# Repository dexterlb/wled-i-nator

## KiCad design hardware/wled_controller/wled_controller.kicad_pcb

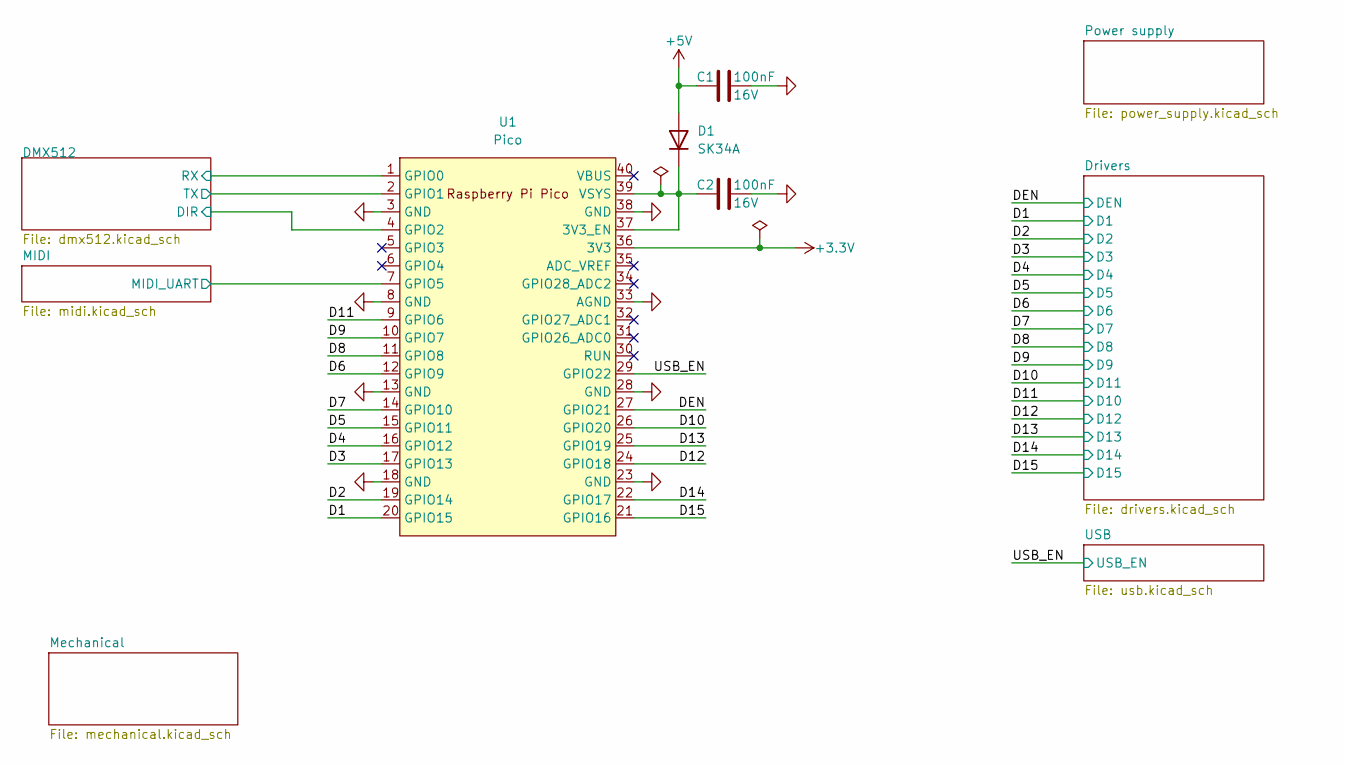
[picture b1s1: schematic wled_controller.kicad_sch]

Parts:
C1, C2: 100nF; C_0805_2012Metric; Part C 100nF 16V 0805
D1: SK34A; D_SMA; Part SK34A
U1: Pico; RPi_Pico_TH; Part 2x Header_01x20

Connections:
+3.3V: U1.36 (3V3); also elsewhere on the board
+5V: C1.1, D1.2 (A); also elsewhere on the board
/D1: U1.20 (GPIO15); also elsewhere on the board
/D2: U1.19 (GPIO14); also elsewhere on the board
/D3: U1.17 (GPIO13); also elsewhere on the board
/D4: U1.16 (GPIO12); also elsewhere on the board
/D5: U1.15 (GPIO11); also elsewhere on the board
/D6: U1.12 (GPIO9); also elsewhere on the board
/D7: U1.14 (GPIO10); also elsewhere on the board
/D8: U1.11 (GPIO8); also elsewhere on the board
/D9: U1.10 (GPIO7); also elsewhere on the board
/D10: U1.26 (GPIO20); also elsewhere on the board
/D11: U1.9 (GPIO6); also elsewhere on the board
/D12: U1.24 (GPIO18); also elsewhere on the board
/D13: U1.25 (GPIO19); also elsewhere on the board
/D14: U1.22 (GPIO17); also elsewhere on the board
/D15: U1.21 (GPIO16); also elsewhere on the board
/DEN: U1.27 (GPIO21); also elsewhere on the board
/DMX512/DIR: U1.4 (GPIO2); also elsewhere on the board
/DMX512/RX: U1.1 (GPIO0); also elsewhere on the board
/DMX512/TX: U1.2 (GPIO1); also elsewhere on the board
/MIDI/MIDI_UART: U1.7 (GPIO5); also elsewhere on the board
/USB_EN: U1.29 (GPIO22); also elsewhere on the board
GND: C1.2, C2.2, U1.3 (GND), U1.8 (GND), U1.13 (GND), U1.18 (GND), U1.23 (GND), U1.28 (GND), U1.33 (AGND), U1.38 (GND); also elsewhere on the board
unnamed: C2.1, D1.1 (K), U1.37 (3V3_EN), U1.39 (VSYS)

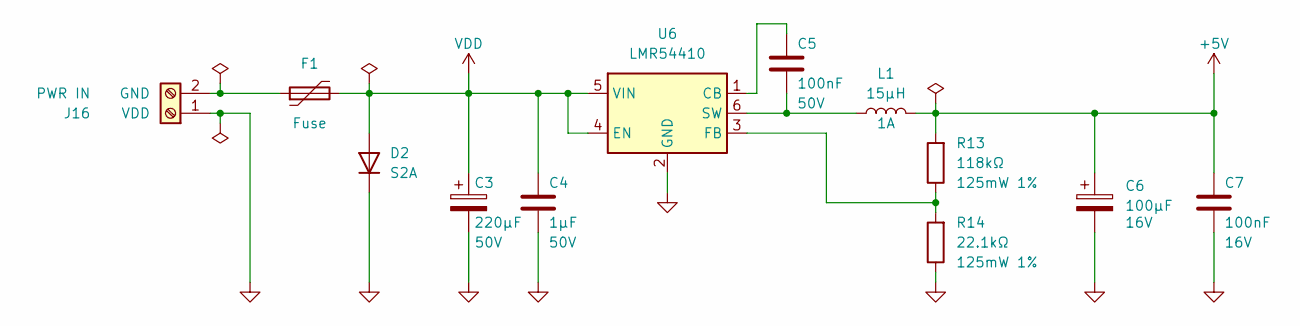
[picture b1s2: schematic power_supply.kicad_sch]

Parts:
C3: 220μF; CP_Radial_D10.0mm_P5.00mm; Part C 220μF 50V P5
C4: 1μF; C_0805_2012Metric; Part C 1μF 50V 0805
C5: 100nF; C_0805_2012Metric; Part C 100nF 50V 0805
C6: 100μF; CP_Radial_D5.0mm_P2.00mm; Part C 100μF 16V P2
C7: 100nF; C_0805_2012Metric; Part C 100nF 16V 0805
D2: S2A; D_SMB; Part S2A; LCSC C7420368
F1: Fuse; Fuseholder_FS002; Part 2x FS-002
J16: Screw_Terminal_01x02; TerminalBlock_1x02_P5.00mm_Horizontal; Part DG127-5.0-02P-14-00AH
L1: 15μH; L_Changjiang_FNR6045S; Part NRS6045T150MMGK
R13: 118kΩ; R_0805_2012Metric; Part R 118kΩ 125mW 1% 0805
R14: 22.1kΩ; R_0805_2012Metric; Part R 22.1kΩ 125mW 1% 0805
U6: LMR54410; SOT-23-6; Part LMR54410FDBVR

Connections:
+5V: C6.1, C7.1, L1.2, R13.2; also elsewhere on the board
GND: C3.2, C4.2, C6.2, C7.2, D2.1 (K), J16.1, R14.1, U6.2 (GND); also elsewhere on the board
unnamed: F1.1, J16.2
unnamed: C5.1, U6.1 (CB)
unnamed: R13.1, R14.2, U6.3 (FB)
unnamed: C5.2, L1.1, U6.6 (SW)
VDD: C3.1, C4.1, D2.2 (A), F1.2, U6.4 (EN), U6.5 (VIN); also elsewhere on the board

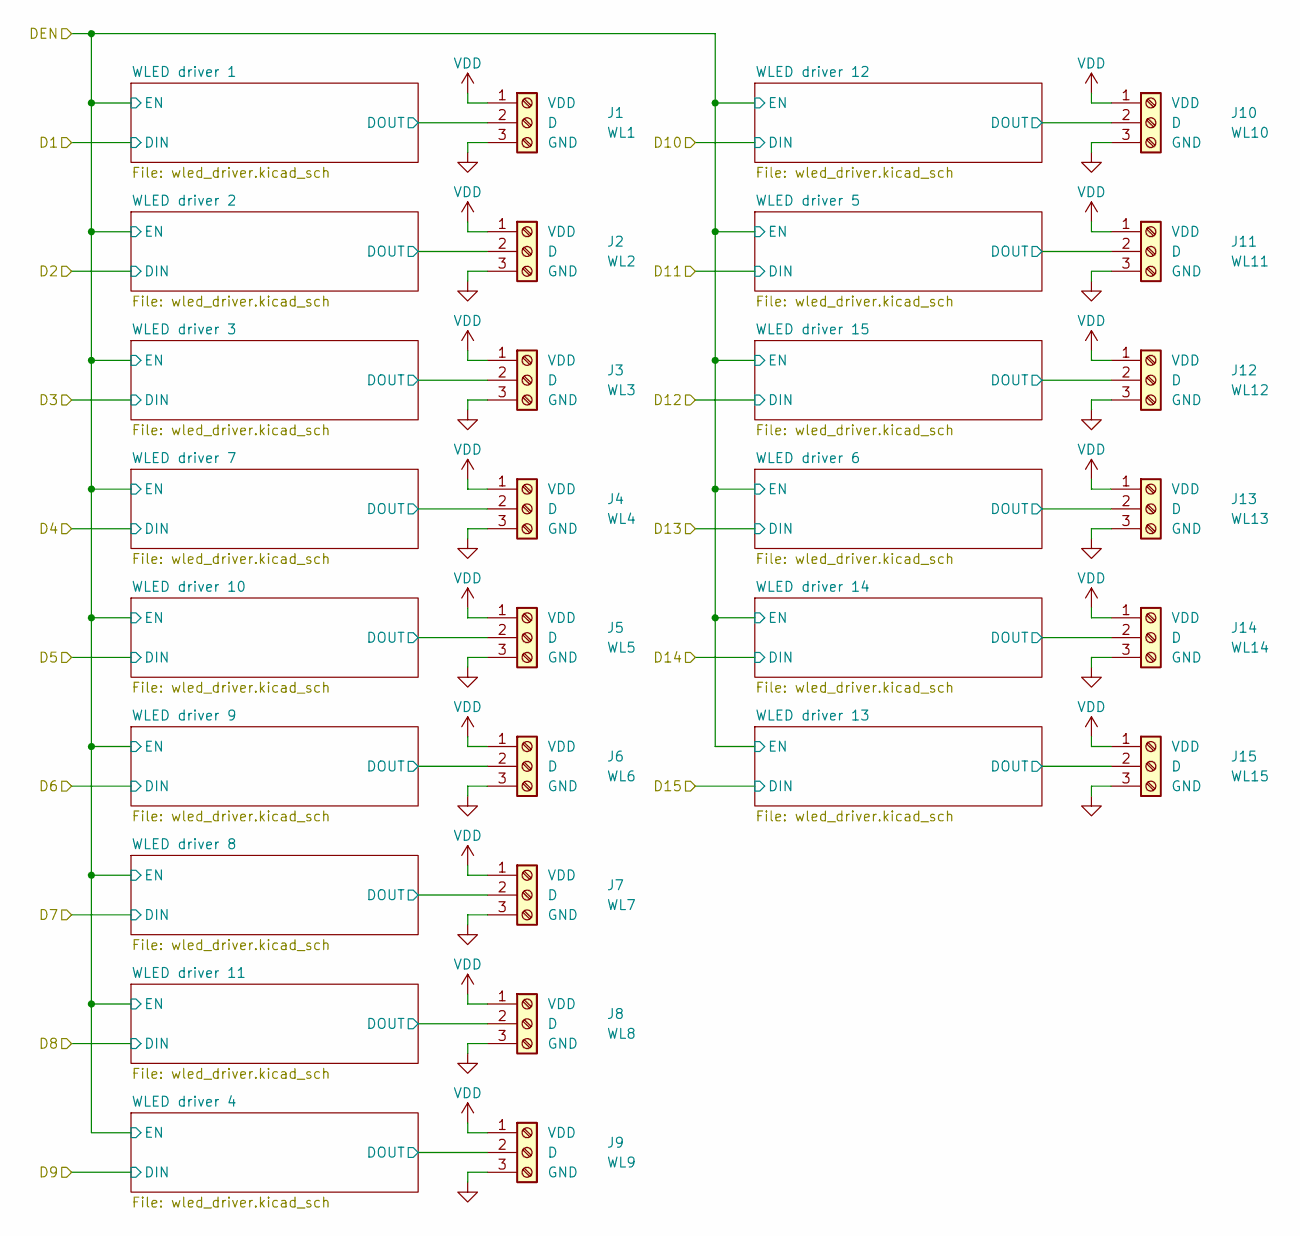
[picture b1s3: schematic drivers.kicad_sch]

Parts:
J1, J2, J3, J4, J5, J6, J7, J8, J9, J10, J11, J12, J13, J14, J15: Screw_Terminal_01x03; TerminalBlock_Degson_1x03_P3.50mm_Horizontal; Part 15EDGRC-3.5-03P-14-00AH, 15EDGK-3.5-03P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

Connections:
/Drivers/WLED driver 1/DOUT: J1.2; also elsewhere on the board
/Drivers/WLED driver 2/DOUT: J2.2; also elsewhere on the board
/Drivers/WLED driver 3/DOUT: J3.2; also elsewhere on the board
/Drivers/WLED driver 4/DOUT: J9.2; also elsewhere on the board
/Drivers/WLED driver 5/DOUT: J11.2; also elsewhere on the board
/Drivers/WLED driver 6/DOUT: J13.2; also elsewhere on the board
/Drivers/WLED driver 7/DOUT: J4.2; also elsewhere on the board
/Drivers/WLED driver 8/DOUT: J7.2; also elsewhere on the board
/Drivers/WLED driver 9/DOUT: J6.2; also elsewhere on the board
/Drivers/WLED driver 10/DOUT: J5.2; also elsewhere on the board
/Drivers/WLED driver 11/DOUT: J8.2; also elsewhere on the board
/Drivers/WLED driver 12/DOUT: J10.2; also elsewhere on the board
/Drivers/WLED driver 13/DOUT: J15.2; also elsewhere on the board
/Drivers/WLED driver 14/DOUT: J14.2; also elsewhere on the board
/Drivers/WLED driver 15/DOUT: J12.2; also elsewhere on the board
GND: J1.3, J2.3, J3.3, J4.3, J5.3, J6.3, J7.3, J8.3, J9.3, J10.3, J11.3, J12.3, J13.3, J14.3, J15.3; also elsewhere on the board
VDD: J1.1, J2.1, J3.1, J4.1, J5.1, J6.1, J7.1, J8.1, J9.1, J10.1, J11.1, J12.1, J13.1, J14.1, J15.1; also elsewhere on the board

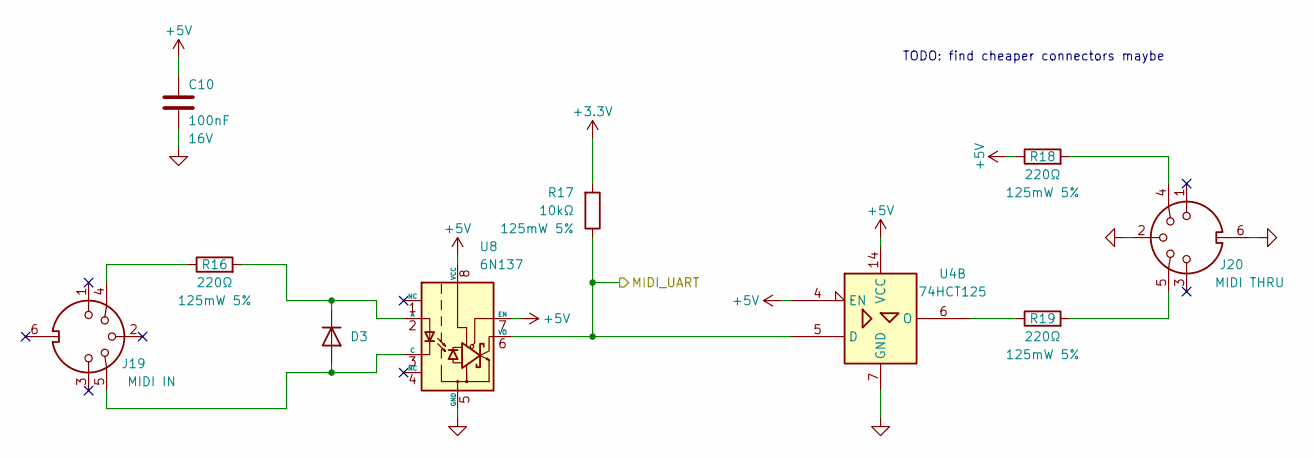
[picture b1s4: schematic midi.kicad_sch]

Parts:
C10: 100nF; C_0805_2012Metric; Part C 100nF 16V 0805
D3: 1N4148WS; D_SOD-323_HandSoldering; Part 1N4148WS
J19, J20: DIN-5_180degree; DIN5_57PC5F; Part 57PC5F
R16, R18, R19: 220Ω; R_0805_2012Metric; Part R 220Ω 125mW 5% 0805
R17: 10kΩ; R_0805_2012Metric; Part R 10kΩ 125mW 1% 0805
U4: 74HCT125; SO-14_5.3x10.2mm_P1.27mm; Part 74HCT125D
U8: 6N137; SMDIP-8_W9.53mm; Part 6N137S SMD

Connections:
+3.3V: R17.2; also elsewhere on the board
+5V: C10.1, R18.1, U4.4 (EN), U4.14 (VCC), U8.7 (EN), U8.8 (VCC); also elsewhere on the board
/D1: U4.9 (D); also elsewhere on the board
/D3: U4.2 (D); also elsewhere on the board
/DEN: U4.1 (EN), U4.10 (EN); also elsewhere on the board
/MIDI/MIDI_UART: R17.1, U4.5 (D), U8.6 (VO); also elsewhere on the board
GND: C10.2, J20.2, J20.6, U4.7 (GND), U8.5 (GND); also elsewhere on the board
unnamed: D3.2 (A), J19.5, U8.3 (C)
unnamed: D3.1 (K), R16.2, U8.2 (A)
unnamed: J19.4, R16.1
unnamed: J20.4, R18.2
unnamed: J20.5, R19.2
unnamed 65: U4.3 (O); also elsewhere on the board
unnamed: R19.1, U4.6 (O)
unnamed 67: U4.8 (O); also elsewhere on the board

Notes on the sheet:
TODO: find cheaper connectors maybe

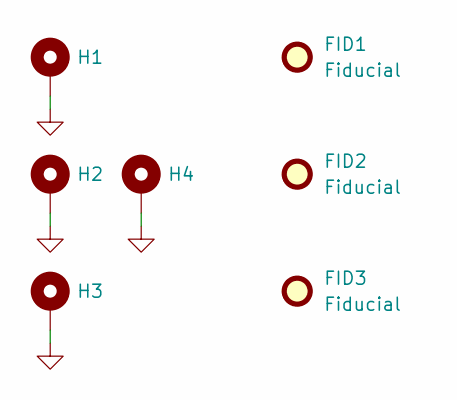
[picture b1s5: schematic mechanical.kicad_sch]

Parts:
FID1, FID2, FID3: Fiducial; Fiducial_1mm_Mask2mm
H1, H2, H3, H4: MountingHole_Pad; MountingHole_3.2mm_M3_DIN965_Pad

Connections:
GND: H1.1, H2.1, H3.1, H4.1; also elsewhere on the board

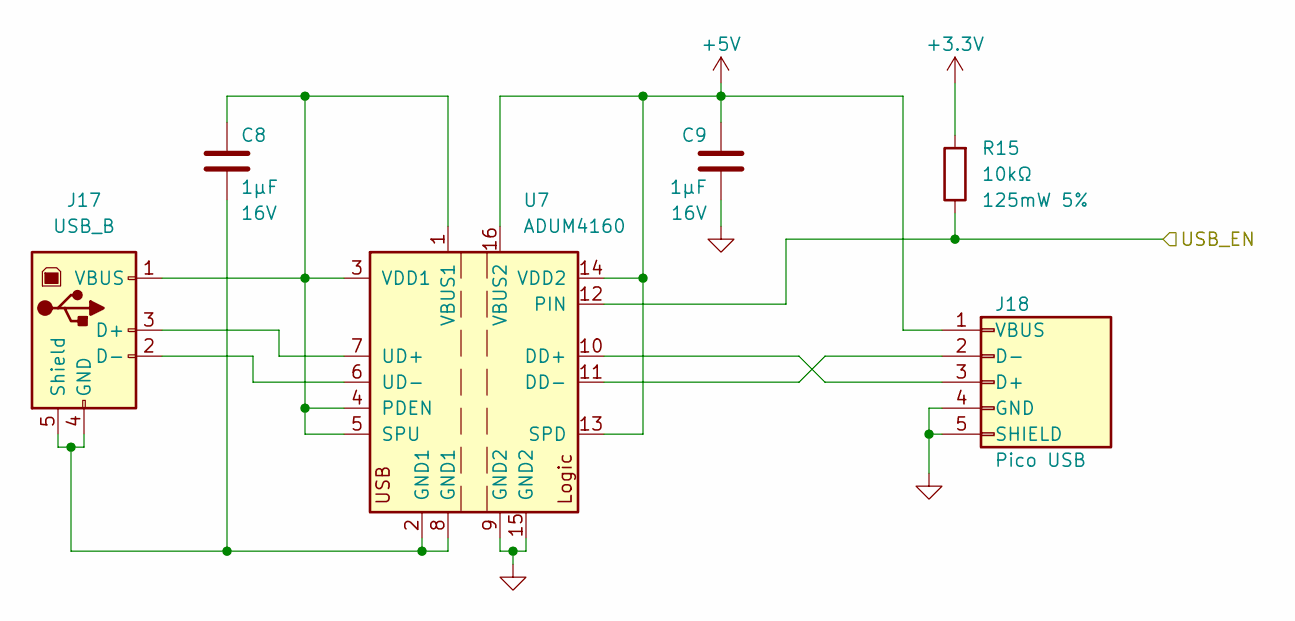
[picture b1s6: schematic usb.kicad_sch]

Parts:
C8, C9: 1μF; C_0805_2012Metric; Part C 1μF 16V 0805
J17: USB_B; USB_B_Lumberg_2411_02_Horizontal; Part 61729-0010BLF
J18: Header_01x05; PinHeader_1x05_P2.54mm_Vertical; Part Header_01x05
R15: 10kΩ; R_0805_2012Metric; Part R 10kΩ 125mW 1% 0805
U7: ADUM4160; SOIC-16W_7.5x10.3mm_P1.27mm; Part ADUM4160BRWZ

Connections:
+3.3V: R15.2; also elsewhere on the board
+5V: C9.1, J18.1, U7.13 (SPD), U7.14 (VDD2), U7.16 (VBUS2); also elsewhere on the board
/USB_EN: R15.1, U7.12 (PIN); also elsewhere on the board
GND: C9.2, J18.4, J18.5, U7.9 (GND2), U7.15 (GND2); also elsewhere on the board
unnamed: J17.3 (D+), U7.7 (UD+)
unnamed: J17.2 (D-), U7.6 (UD-)
unnamed: C8.2, J17.4 (GND), J17.5 (Shield), U7.2 (GND1), U7.8 (GND1)
unnamed: C8.1, J17.1 (VBUS), U7.1 (VBUS1), U7.3 (VDD1), U7.4 (PDEN), U7.5 (SPU)
unnamed: J18.2, U7.11 (DD-)
unnamed: J18.3, U7.10 (DD+)

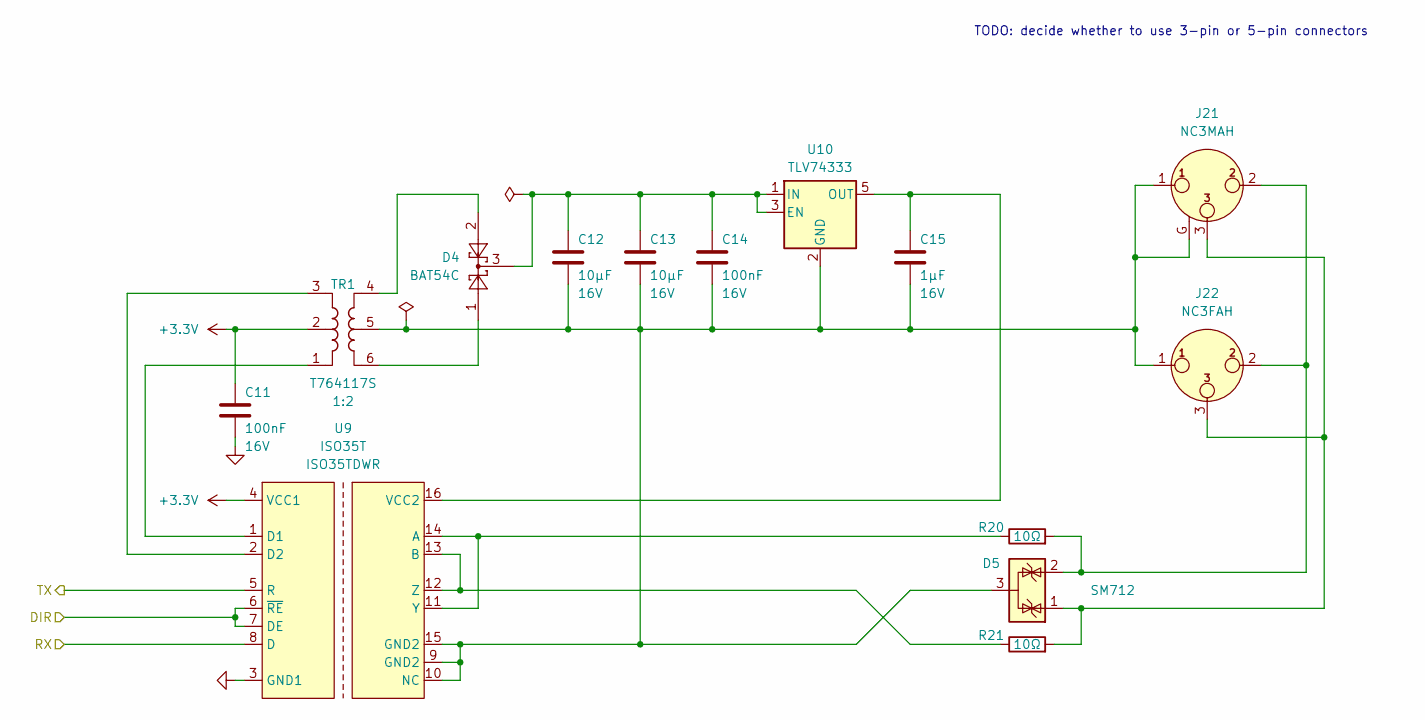
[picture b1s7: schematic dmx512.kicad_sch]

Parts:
C11, C14: 100nF; C_0805_2012Metric; Part C 100nF 16V 0805
C12, C13: 10μF; C_0805_2012Metric; Part C 10μF 16V 0805
C15: 1μF; C_0805_2012Metric; Part C 1μF 16V 0805
D4: BAT54C; SOT-23; Part BAT54C
D5: SM712; SOT-23
J21: NC3MAH; Jack_XLR_Neutrik_NC3MAH_Horizontal; Part NC3MAH
J22: NC3FAH; Jack_XLR_Neutrik_NC3FAH_Horizontal; Part NC3FAH
R20, R21: 10Ω; R_0805_2012Metric
TR1: T764117S; Bourns_PAD00x-T764; Part PAD001-T764120S
U9: ISO35T; SOIC-16W_7.5x10.3mm_P1.27mm; Part ISO35TDWR
U10: TLV74333; SOT-23-5; Part TLV74333PDBVR

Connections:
+3.3V: C11.1, TR1.2, U9.4 (VCC1); also elsewhere on the board
/DMX512/DIR: U9.6 (~RE), U9.7 (DE); also elsewhere on the board
/DMX512/RX: U9.8 (D); also elsewhere on the board
/DMX512/TX: U9.5 (R); also elsewhere on the board
GND: C11.2, U9.3 (GND1); also elsewhere on the board
unnamed: D4.1, TR1.6
unnamed: D4.2, TR1.4
unnamed: C12.2, C13.2, C14.2, C15.2, D5.3 (A), J21.1, J21.G, J22.1, TR1.5, U9.9 (GND2), U9.10 (NC), U9.15 (GND2), U10.2 (GND)
unnamed: D5.1 (K), J21.3, J22.3, R21.2
unnamed: D5.2 (K), J21.2, J22.2, R20.2
unnamed: R20.1, U9.11 (Y), U9.14 (A)
unnamed: R21.1, U9.12 (Z), U9.13 (B)
unnamed: TR1.1, U9.1 (D1)
unnamed: TR1.3, U9.2 (D2)
unnamed: C12.1, C13.1, C14.1, D4.3, U10.1 (IN), U10.3 (EN)
unnamed: C15.1, U9.16 (VCC2), U10.5 (OUT)

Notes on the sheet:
TODO: decide whether to use 3-pin or 5-pin connectors

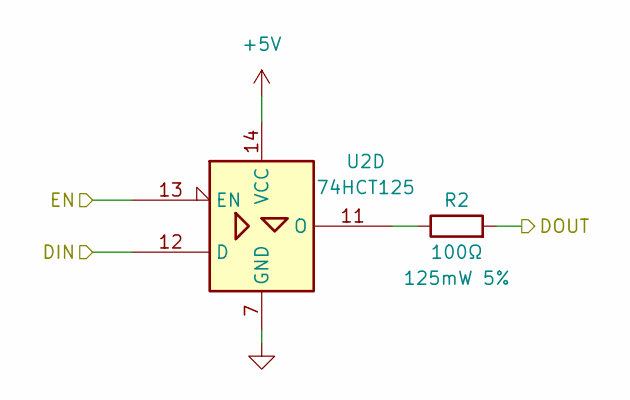
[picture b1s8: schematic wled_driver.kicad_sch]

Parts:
R2: 100Ω; R_0805_2012Metric; Part RC0805JR-07100RL
U2: 74HCT125; SO-14_5.3x10.2mm_P1.27mm; Part 74HCT125D

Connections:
+5V: U2.14 (VCC); also elsewhere on the board
/D4: U2.9 (D); also elsewhere on the board
/D5: U2.5 (D); also elsewhere on the board
/D6: U2.2 (D); also elsewhere on the board
/D7: U2.12 (D); also elsewhere on the board
/DEN: U2.1 (EN), U2.4 (EN), U2.10 (EN), U2.13 (EN); also elsewhere on the board
/Drivers/WLED driver 8/DOUT: R2.2; also elsewhere on the board
GND: U2.7 (GND); also elsewhere on the board
unnamed 57: U2.3 (O); also elsewhere on the board
unnamed 58: U2.6 (O); also elsewhere on the board
unnamed 59: U2.8 (O); also elsewhere on the board
unnamed: R2.1, U2.11 (O)

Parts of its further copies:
R1, R3, R4, R5, R6, R7, R8, R9, R10, R11, R12, R22, R23, R24: 100Ω; R_0805_2012Metric; Part RC0805JR-07100RL
U3, U5: 74HCT125; SO-14_5.3x10.2mm_P1.27mm; Part 74HCT125D

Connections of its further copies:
+5V: U3.14 (VCC), U5.14 (VCC); also elsewhere on the board
/D8: U3.9 (D); also elsewhere on the board
/D9: U3.5 (D); also elsewhere on the board
/D10: U3.2 (D); also elsewhere on the board
/D11: U3.12 (D); also elsewhere on the board
/D12: U5.9 (D); also elsewhere on the board
/D13: U5.12 (D); also elsewhere on the board
/D14: U5.5 (D); also elsewhere on the board
/D15: U5.2 (D); also elsewhere on the board
/DEN: U3.1 (EN), U3.4 (EN), U3.10 (EN), U3.13 (EN), U5.1 (EN), U5.4 (EN), U5.10 (EN), U5.13 (EN); also elsewhere on the board
/Drivers/WLED driver 1/DOUT: R7.2; also elsewhere on the board
/Drivers/WLED driver 2/DOUT: R8.2; also elsewhere on the board
/Drivers/WLED driver 3/DOUT: R9.2; also elsewhere on the board
/Drivers/WLED driver 4/DOUT: R10.2; also elsewhere on the board
/Drivers/WLED driver 5/DOUT: R11.2; also elsewhere on the board
/Drivers/WLED driver 6/DOUT: R12.2; also elsewhere on the board
/Drivers/WLED driver 7/DOUT: R1.2; also elsewhere on the board
/Drivers/WLED driver 9/DOUT: R3.2; also elsewhere on the board
/Drivers/WLED driver 10/DOUT: R4.2; also elsewhere on the board
/Drivers/WLED driver 11/DOUT: R5.2; also elsewhere on the board
/Drivers/WLED driver 12/DOUT: R6.2; also elsewhere on the board
/Drivers/WLED driver 13/DOUT: R22.2; also elsewhere on the board
/Drivers/WLED driver 14/DOUT: R23.2; also elsewhere on the board
/Drivers/WLED driver 15/DOUT: R24.2; also elsewhere on the board
GND: U3.7 (GND), U5.7 (GND); also elsewhere on the board
unnamed 57: R3.1; also elsewhere on the board
unnamed 58: R4.1; also elsewhere on the board
unnamed 59: R1.1; also elsewhere on the board
unnamed: R11.1, U3.3 (O)
unnamed: R10.1, U3.6 (O)
unnamed: R5.1, U3.8 (O)
unnamed: R6.1, U3.11 (O)
unnamed 65: R9.1; also elsewhere on the board
unnamed 67: R7.1; also elsewhere on the board
unnamed 68: R8.1; also elsewhere on the board
unnamed: R22.1, U5.3 (O)
unnamed: R23.1, U5.6 (O)
unnamed: R24.1, U5.8 (O)
unnamed: R12.1, U5.11 (O)

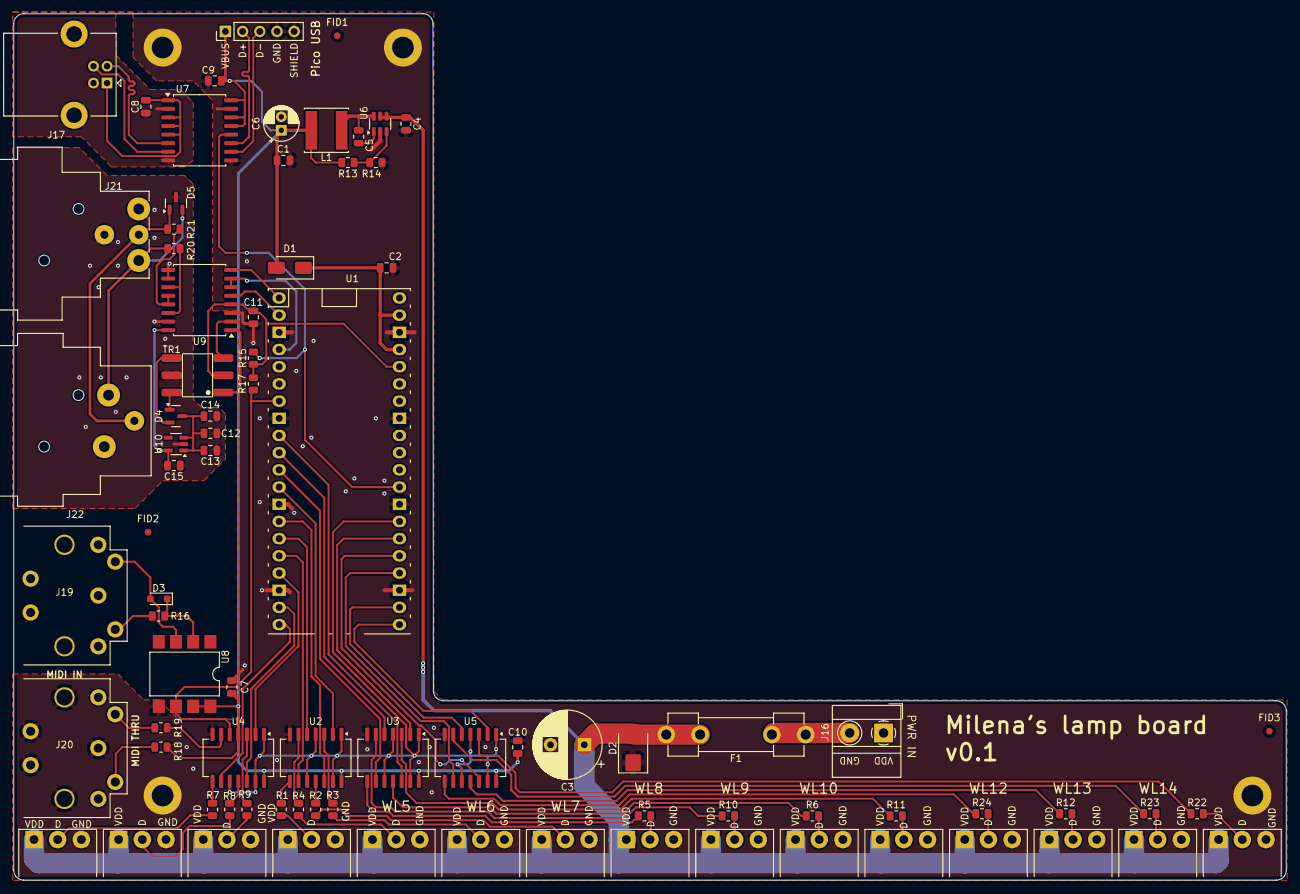
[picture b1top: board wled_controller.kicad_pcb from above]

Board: 2 copper layers, 188.0 x 128.0 mm, 86 parts (0 on the bottom side), 83 nets.

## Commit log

2024-08-09 add pcb
2024-08-09 finalise schematic
2024-08-12 some progress on PCB
2024-08-14 work on pcb
2024-08-14 dmx512 line TVS
2024-08-14 final pcb touches
2024-08-26 update bom
